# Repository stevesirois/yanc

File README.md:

# YANC
Y.A.N.C. - Yet Another Nixie Clock

This project is the software part of a larger project that include nixie tube clock with no physical controls but only "web" access.

The physical construction will be publish on Instructables (http://www.instructables.com/)

The project is two parts:

Physical part - Nixie Clock

- 4 nixie tubes (IN-14) display
- Raspberry PI Model A+ (256MB) for main controller
- Custom nixie driver circuit and audio ouput (PCB)
- MP3 Playback for alarm
- Sound activated display (extented life of tubes)

Software part - Clock control and remote app

- Controler daemon for clock hardware control (Python)
- REST Server to interact with external world (look mom, no button!)
- IOS App to "talk" to the clock (Swift)

Simply put, this clock will look great, will sync itself on the Net and get it's alarms from my Google Calendar! :-)

More details coming...

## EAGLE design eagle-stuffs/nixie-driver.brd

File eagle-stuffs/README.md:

# Eagle 7.2 files
The .sch and .brd files are Eagle CAD schematic and PCB design files.

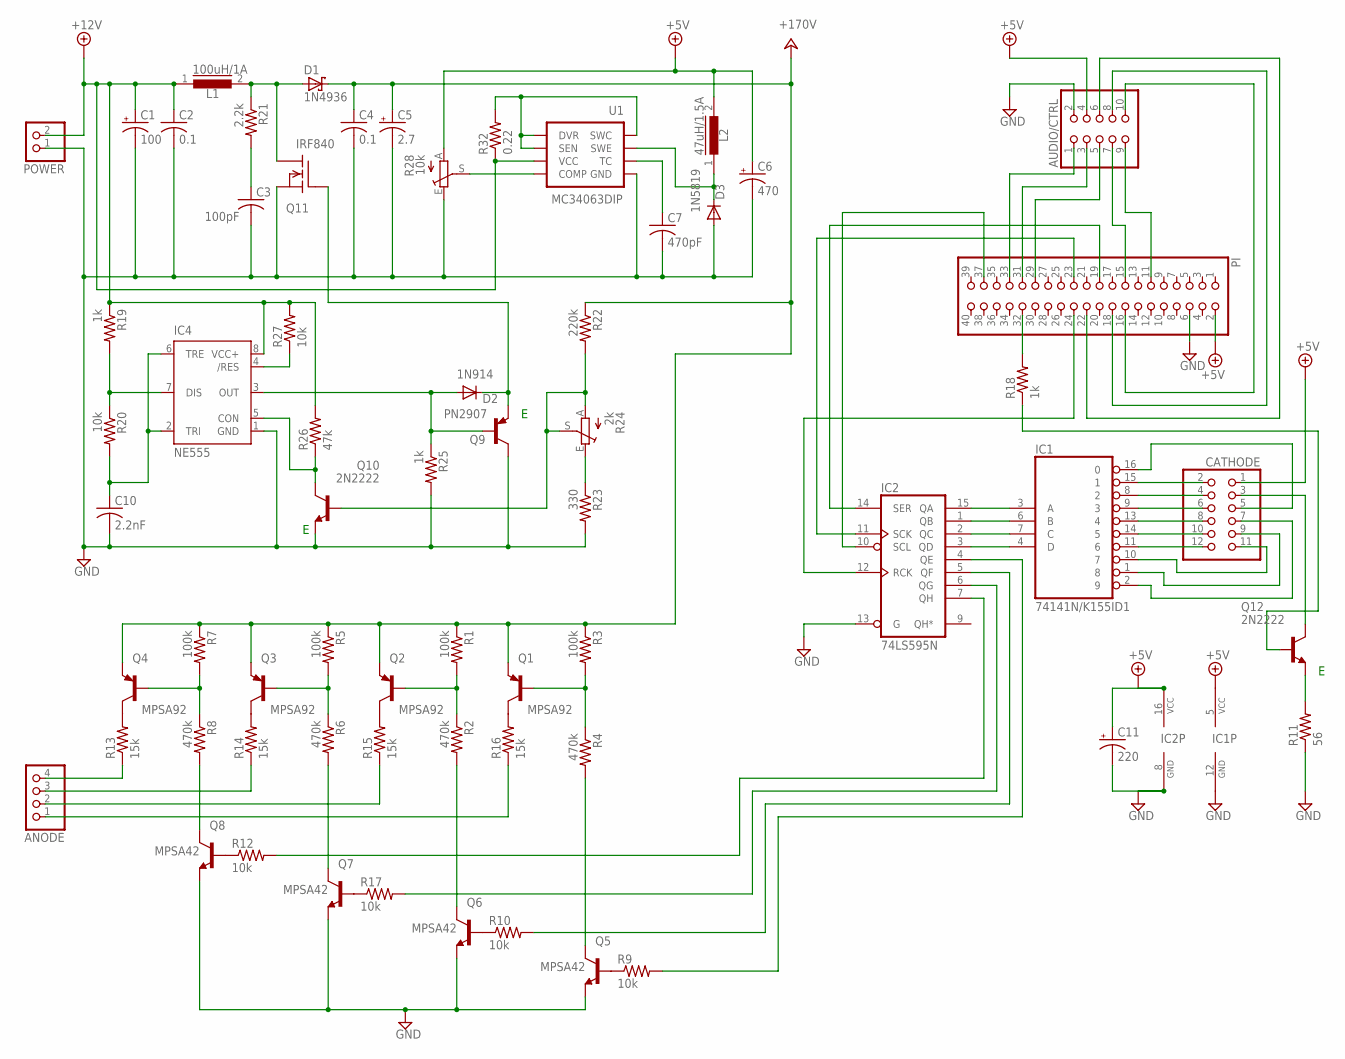
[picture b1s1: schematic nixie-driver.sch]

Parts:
ANODE: PINHD-1X4; 1X04
AUDIO/CTRL: PINHD-2X5; 2X05
C1: 100; E2,5-6E
C2: 0.1; C050-024X044
C3: 100pF; C050-024X044
C4: 0.1; C150-054X183
C5: 2.7; E2,5-7
C6: 470; E3,5-8
C7: 470pF; C050-024X044
C10: 2.2nF; C025-025X050
C11: 220; E3,5-8
CATHODE: PINHD-2X6; 2X06
D1: 1N4936; DO41-7.6
D2: 1N914; DO41-10
D3: 1N5819; DO41-10
IC1: 74141N/K155ID1; DIL16
IC2: 74LS595N; DIL16
IC4: NE555; DIL-08
L1: 100uH/1A; MMICC7
L2: 47uH/1.5A; MMICC7
PI: PINHD-2X20; 2X20
POWER: PINHD-1X2; 1X02
Q1, Q2, Q3, Q4: MPSA92; TO92-EBC
Q5, Q6, Q7, Q8: MPSA42; TO92-EBC
Q9: PN2907; TO92-CBE
Q10, Q12: 2N2222; TO92-EBC
Q11: IRF840; TO220
R1, R3, R5, R7: 100k; 0207/10
R2, R4, R6, R8: 470k; 0207/10
R9, R10, R12, R17, R20, R27: 10k; 0207/10
R11: 56; 0207/10
R13, R14, R15, R16: 15k; 0207/10
R18, R19, R25: 1k; 0207/10
R21: 2.2k; 0207/10
R22: 220k; 0207/10
R23: 330; 0207/10
R24: 2k; CA6V
R26: 47k; 0207/10
R28: 10k; CA6V
R32: 0.22; 0204V
U1: MC34063DIP; DIP-08

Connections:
+5V: AUDIO/CTRL.4, C6.+, C11.+, CATHODE.1, IC1.5 (VCC), IC2.16 (VCC), L2.2, PI.2, R28.A
+12V: C1.+, C2.1, IC4.8 (VCC+), L1.1, POWER.2, R19.1, R26.2, R27.2, R32.1, U1.6 (VCC)
+24V: C4.1, C5.+, D1.C, Q1.E, Q2.E, Q3.E, Q4.E, R1.1, R3.1, R5.1, R7.1, R22.1
GND: AUDIO/CTRL.2, C1.-, C2.2, C3.2, C4.2, C5.-, C6.-, C7.2, C10.2, C11.-, D3.A, IC1.12 (GND), IC2.8 (GND), IC2.13 (G), IC4.1 (GND), PI.6, POWER.1, Q5.E, Q6.E, Q7.E, Q8.E, Q9.C, Q10.E, Q11.3 (S), R11.1, R23.2, R25.2, R28.E, U1.4 (GND)
unnamed: D1.A, L1.2, Q11.2 (D), R21.1
unnamed: CATHODE.2, IC1.15 (1)
unnamed: CATHODE.4, IC1.8 (2)
unnamed: CATHODE.6, IC1.9 (3)
unnamed: CATHODE.8, IC1.13 (4)
unnamed: CATHODE.10, IC1.14 (5)
unnamed: CATHODE.12, IC1.11 (6)
unnamed: CATHODE.11, IC1.10 (7)
unnamed: CATHODE.9, IC1.1 (8)
unnamed: CATHODE.7, IC1.2 (9)
unnamed: CATHODE.5, IC1.16 (0)
unnamed: IC1.3 (A), IC2.15 (QA)
unnamed: IC1.6 (B), IC2.1 (QB)
unnamed: IC1.7 (C), IC2.2 (QC)
unnamed: IC1.4 (D), IC2.3 (QD)
unnamed: PI.32, R18.2
unnamed: Q4.B, R7.2, R8.1
unnamed: Q3.B, R5.2, R6.1
unnamed: Q2.B, R1.2, R2.1
unnamed: Q1.B, R3.2, R4.1
unnamed: Q4.C, R13.2
unnamed: Q3.C, R14.2
unnamed: Q2.C, R15.2
unnamed: Q1.C, R16.2
unnamed: ANODE.4, R13.1
unnamed: ANODE.3, R14.1
unnamed: ANODE.2, R15.1
unnamed: ANODE.1, R16.1
unnamed: Q8.C, R8.2
unnamed: Q8.B, R12.1
unnamed: Q7.B, R17.1
unnamed: Q6.B, R10.1
unnamed: Q5.B, R9.1
unnamed: Q7.C, R6.2
unnamed: Q6.C, R2.2
unnamed: Q5.C, R4.2
unnamed: IC2.7 (QH), R12.2
unnamed: IC2.6 (QG), R17.2
unnamed: IC2.5 (QF), R10.2
unnamed: IC2.4 (QE), R9.2
unnamed: IC2.12 (RCK), PI.24
unnamed: IC2.11 (SCK), PI.23
unnamed: IC2.14 (SER), PI.19
unnamed: Q12.E, R11.2
unnamed: CATHODE.3, Q12.C
unnamed: Q12.B, R18.1
unnamed: AUDIO/CTRL.1, PI.33
unnamed: AUDIO/CTRL.3, PI.31
unnamed: AUDIO/CTRL.5, PI.29
unnamed: AUDIO/CTRL.7, PI.15
unnamed: AUDIO/CTRL.9, PI.11
unnamed: IC4.7 (DIS), R19.2, R20.1
unnamed: AUDIO/CTRL.10, PI.16
unnamed: AUDIO/CTRL.8, PI.18
unnamed: AUDIO/CTRL.6, PI.22
unnamed: C3.1, R21.2
unnamed: R32.2, U1.1 (SWC), U1.7 (SEN), U1.8 (DVR)
unnamed: IC4.4 (/RES), R27.1
unnamed: D2.A, IC4.3 (OUT), Q9.B, R25.1
unnamed: IC4.5 (CON), Q10.C, R26.1
unnamed: R28.S, U1.5 (COMP)
unnamed: D2.C, Q9.E, Q11.1 (G)
unnamed: IC2.10 (SCL), PI.37
unnamed: Q10.B, R22.2, R24.A, R24.S
unnamed: R23.1, R24.E
unnamed: C10.1, IC4.2 (TRI), IC4.6 (TRE), R20.2
unnamed: C7.1, U1.3 (TC)
unnamed: D3.C, L2.1, U1.2 (SWE)

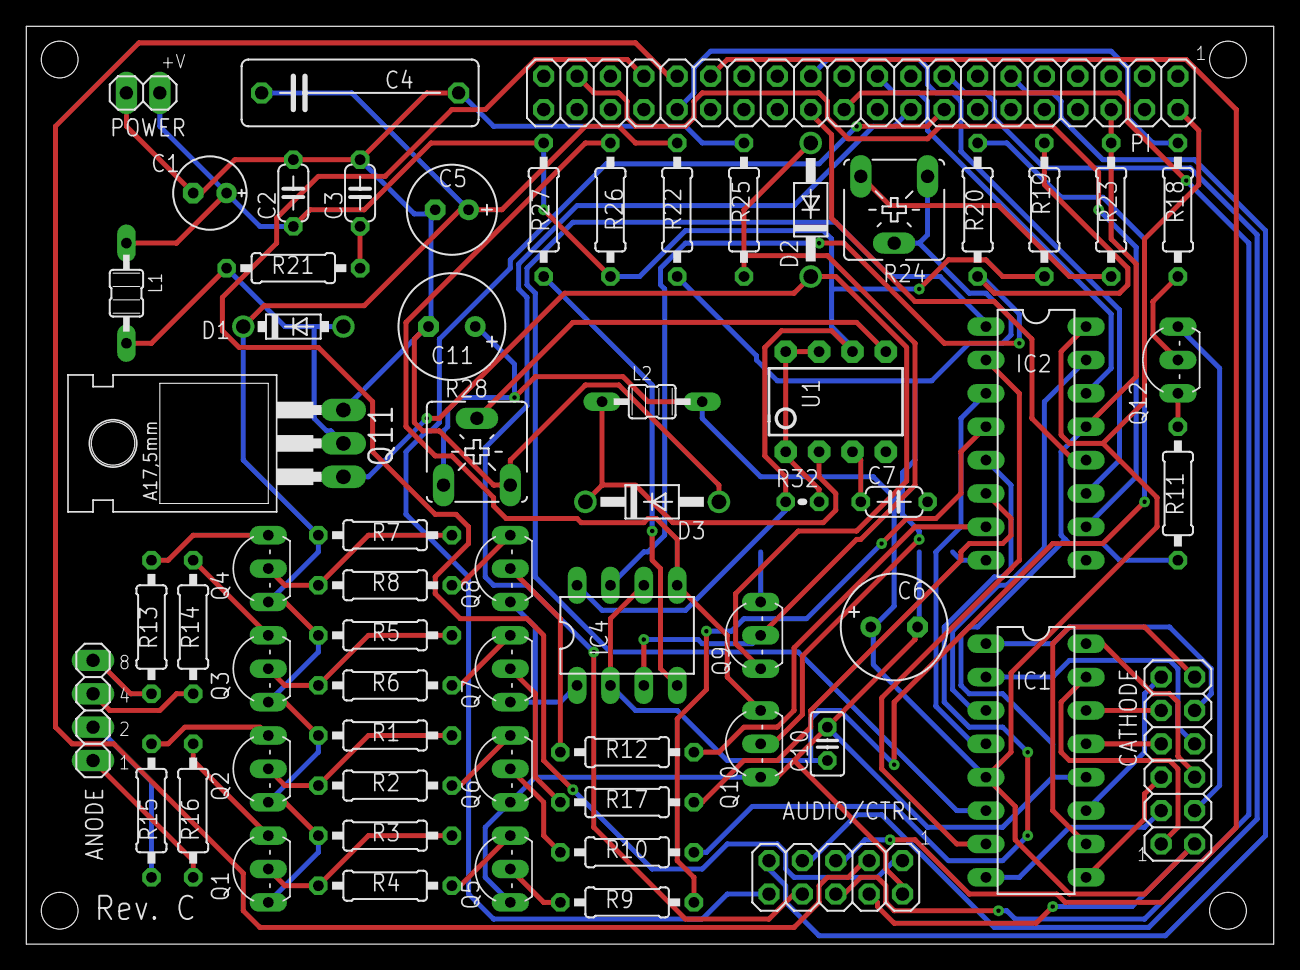
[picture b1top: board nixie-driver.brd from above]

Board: 2 copper layers, 94.9 x 69.8 mm, 64 parts (0 on the bottom side), 72 nets.

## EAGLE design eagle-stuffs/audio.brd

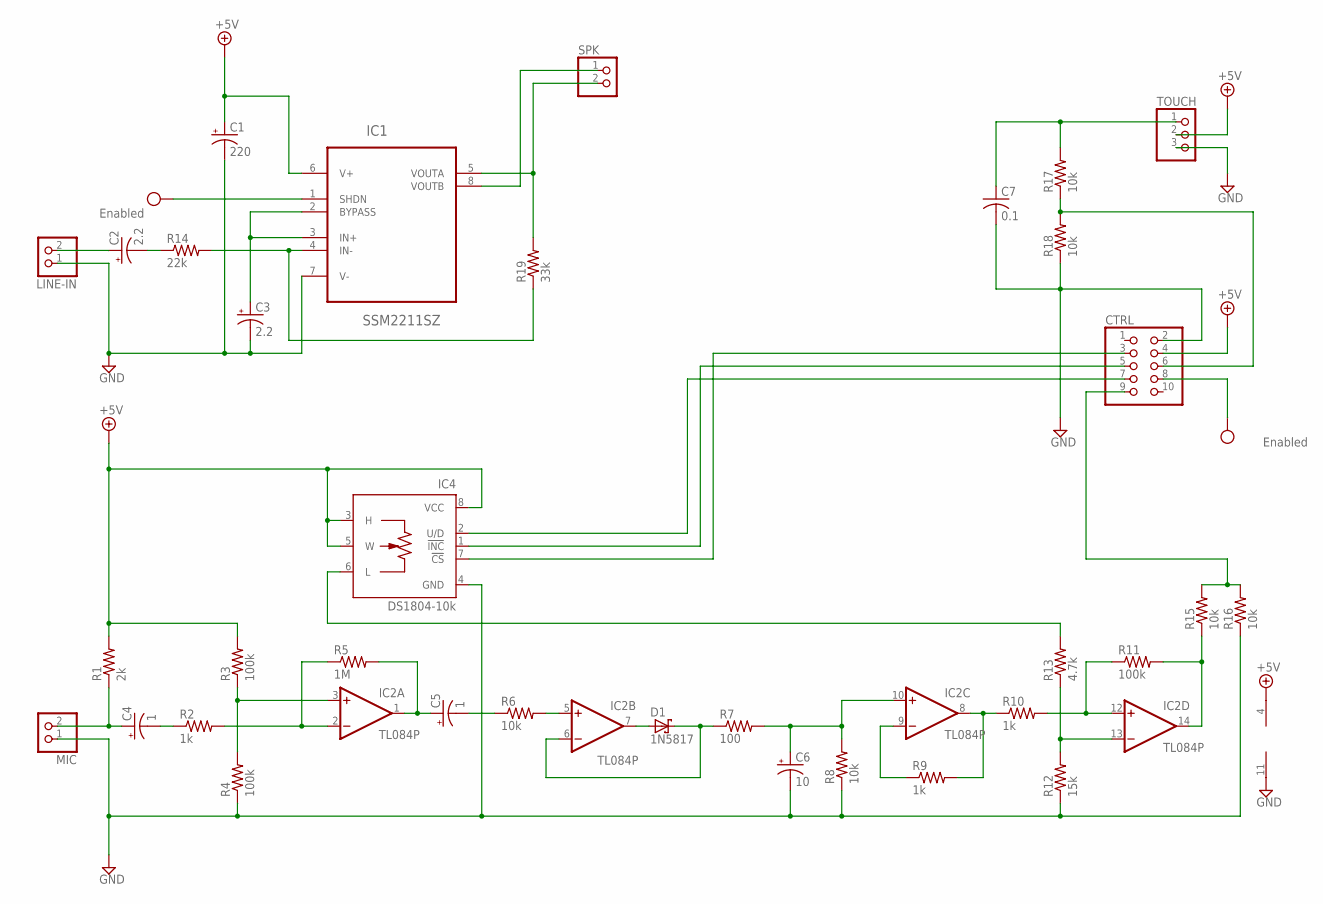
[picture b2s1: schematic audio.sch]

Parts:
C1: 220; E3,5-10
C2, C3: 2.2; E3,5-8
C4, C5: 1; E2-4
C6: 10; E2-4
C7: 0.1; C025-024X044
CTRL: PINHD-2X5; 2X05
D1: 1N5817; DO41-7
IC1: SSM2211SZ; SOIC127P600X175-8N
IC2: TL084P; DIL14
IC4: DS1804-10k; DIL08
LINE-IN: PINHD-1X2; 1X02
MIC: PINHD-1X2; 1X02
R1: 2k; 0204V
R2, R9, R10: 1k; 0204V
R3, R4, R11: 100k; 0204V
R5: 1M; 0204V
R6, R8, R15, R16, R17, R18: 10k; 0204V
R7: 100; 0204V
R12: 15k; 0204V
R13: 4.7k; 0204V
R14: 22k; 0204V
R19: 33k; 0204V
SPK: PINHD-1X2; 1X02
TOUCH: PINHD-1X3; 1X03

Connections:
+5V: C1.+, CTRL.4, IC1.6 (V+), IC2.4 (V+), IC4.3 (H), IC4.5 (W), IC4.8 (VCC), R1.2, R3.2, TOUCH.2
GND: C1.-, C3.-, C6.-, C7.2, CTRL.2, IC1.7 (V-), IC2.11 (V-), IC4.4 (GND), LINE-IN.1, MIC.1, R4.1, R8.1, R12.1, R16.1, R18.1, TOUCH.3
unnamed: IC1.5 (VOUTA), R19.2, SPK.2
unnamed: C2.+, LINE-IN.2
unnamed: C2.-, R14.1
unnamed: IC1.4 (IN-), R14.2, R19.1
unnamed: C3.+, IC1.2 (BYPASS), IC1.3 (IN+)
unnamed: IC1.8 (VOUTB), SPK.1
unnamed: IC4.6 (L), R13.2
unnamed: C4.-, R2.1
unnamed: C4.+, MIC.2, R1.1
unnamed: IC2.2 (-IN), R2.2, R5.1
unnamed: C5.+, IC2.1 (OUT), R5.2
unnamed: C5.-, R6.1
unnamed: IC2.14 (OUT), R11.2, R15.1
unnamed: IC2.3 (+IN), R3.1, R4.2
unnamed: CTRL.9, R15.2, R16.2
unnamed: D1.A, IC2.7 (OUT)
unnamed: IC2.5 (+IN), R6.2
unnamed: CTRL.3, IC4.7 (!CS)
unnamed: CTRL.5, IC4.1 (!INC)
unnamed: CTRL.7, IC4.2 (U/D)
unnamed: D1.C, IC2.6 (-IN), R7.1
unnamed: C6.+, IC2.10 (+IN), R7.2, R8.2
unnamed: IC2.9 (-IN), R9.1
unnamed: IC2.8 (OUT), R9.2, R10.1
unnamed: IC2.12 (+IN), R10.2, R11.1
unnamed: C7.1, R17.2, TOUCH.1
unnamed: IC2.13 (-IN), R12.2, R13.1
unnamed: CTRL.6, R17.1, R18.2
VCC: CTRL.8, IC1.1 (SHDN)

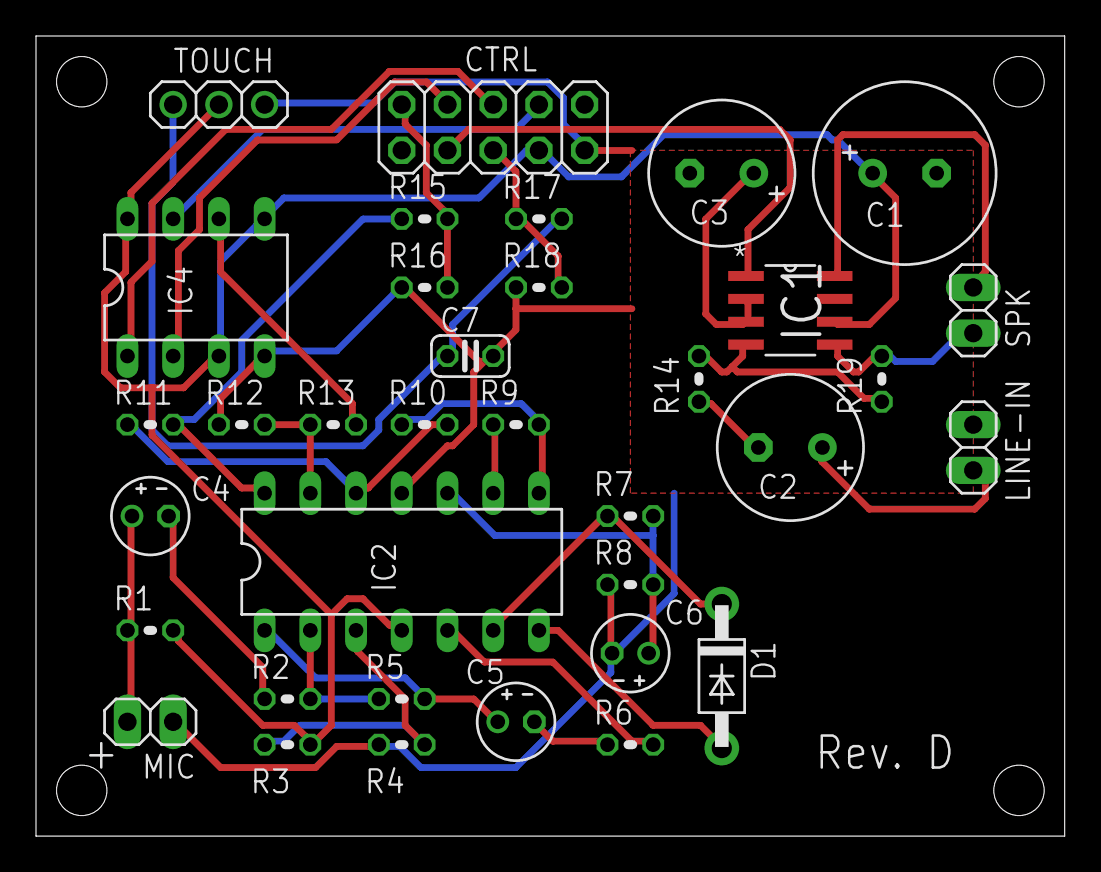
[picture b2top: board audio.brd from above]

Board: 2 copper layers, 57.1 x 44.5 mm, 35 parts (0 on the bottom side), 31 nets.

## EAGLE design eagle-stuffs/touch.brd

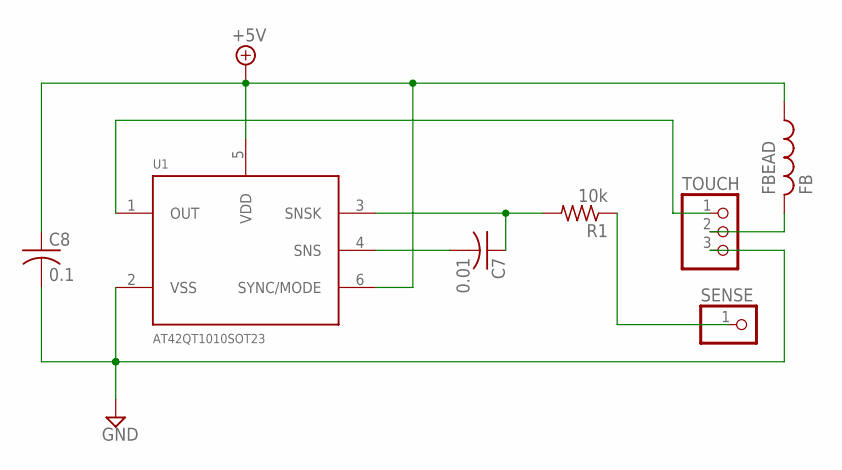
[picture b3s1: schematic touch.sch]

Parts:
C7: 0.01; C025-025X050
C8: 0.1; C025-025X050
FBEAD: FB
R1: 10k; 0207/10
SENSE: PINHD-1X1; 1X01
TOUCH: PINHD-1X3; 1X03
U1: AT42QT1010SOT23; SOT23-6

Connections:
+5V: C8.1, FBEAD.P$1 (1), U1.5 (VDD), U1.6 (SYNC/MODE)
GND: C8.2, TOUCH.3, U1.2 (VSS)
unnamed: TOUCH.1, U1.1 (OUT)
unnamed: R1.1, SENSE.1
unnamed: FBEAD.P$2 (2), TOUCH.2
unnamed: C7.1, R1.2, U1.3 (SNSK)
unnamed: C7.2, U1.4 (SNS)

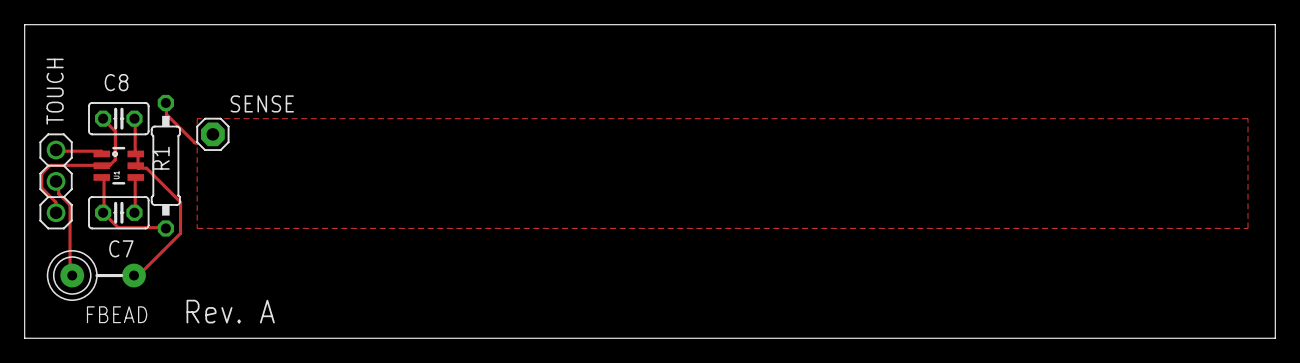
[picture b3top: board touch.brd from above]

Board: 2 copper layers, 101.3 x 25.4 mm, 7 parts (0 on the bottom side), 7 nets.

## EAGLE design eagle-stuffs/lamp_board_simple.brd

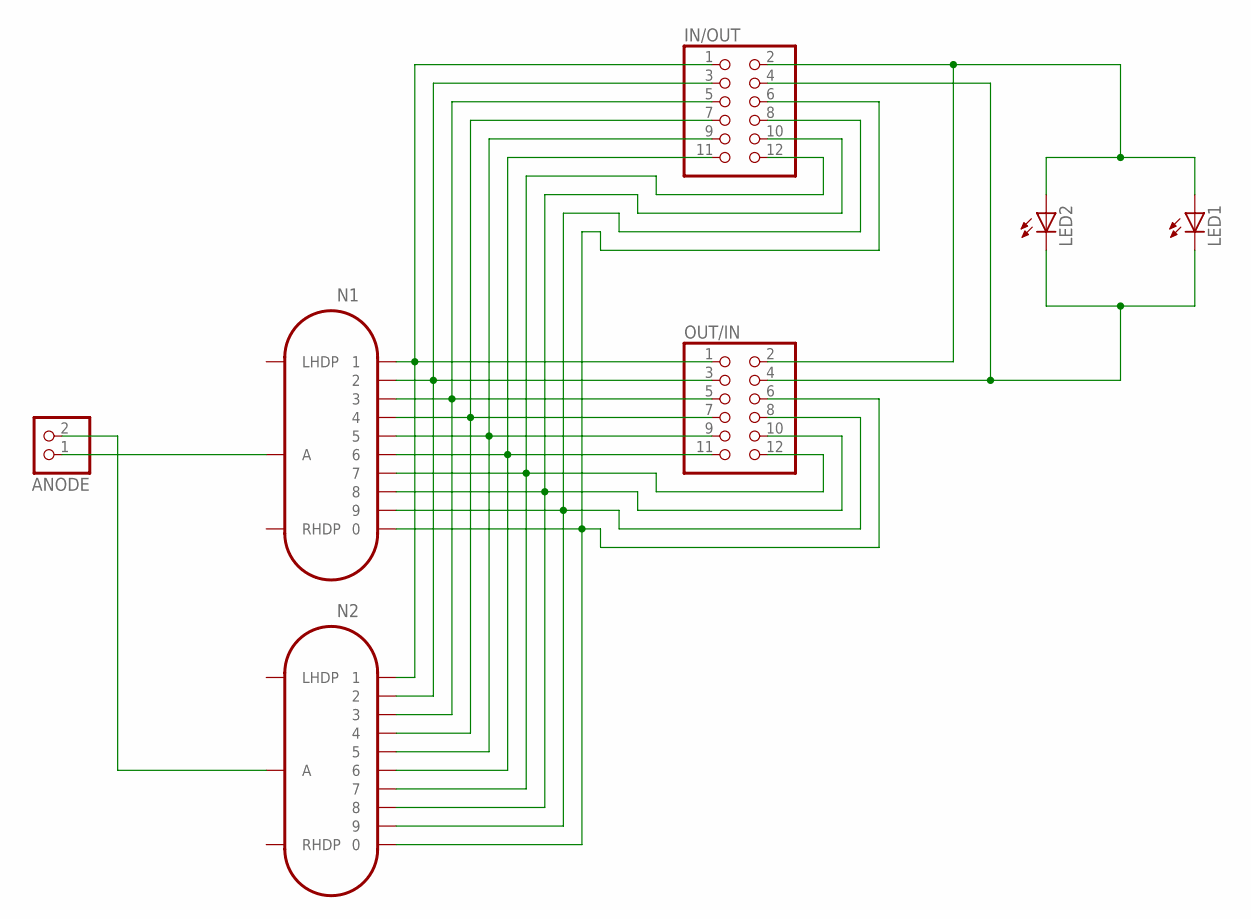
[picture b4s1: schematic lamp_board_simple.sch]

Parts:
ANODE: PINHD-1X2/90; 1X02/90
IN/OUT: PINHD-2X6/90; 2X06/90
LED1, LED2: LED5MM
N1, N2: IN-14
OUT/IN: PINHD-2X6/90; 2X06/90

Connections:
unnamed: ANODE.1, N1.A
unnamed: ANODE.2, N2.A
unnamed: IN/OUT.4, LED1.K (C), LED2.K (C), OUT/IN.4
unnamed: IN/OUT.2, LED1.A, LED2.A, OUT/IN.2
unnamed: IN/OUT.1, N1.1, N2.1, OUT/IN.1
unnamed: IN/OUT.3, N1.2, N2.2, OUT/IN.3
unnamed: IN/OUT.5, N1.3, N2.3, OUT/IN.5
unnamed: IN/OUT.7, N1.4, N2.4, OUT/IN.7
unnamed: IN/OUT.9, N1.5, N2.5, OUT/IN.9
unnamed: IN/OUT.11, N1.6, N2.6, OUT/IN.11
unnamed: IN/OUT.12, N1.7, N2.7, OUT/IN.12
unnamed: IN/OUT.10, N1.8, N2.8, OUT/IN.10
unnamed: IN/OUT.8, N1.9, N2.9, OUT/IN.8
unnamed: IN/OUT.6, N1.0, N2.0, OUT/IN.6

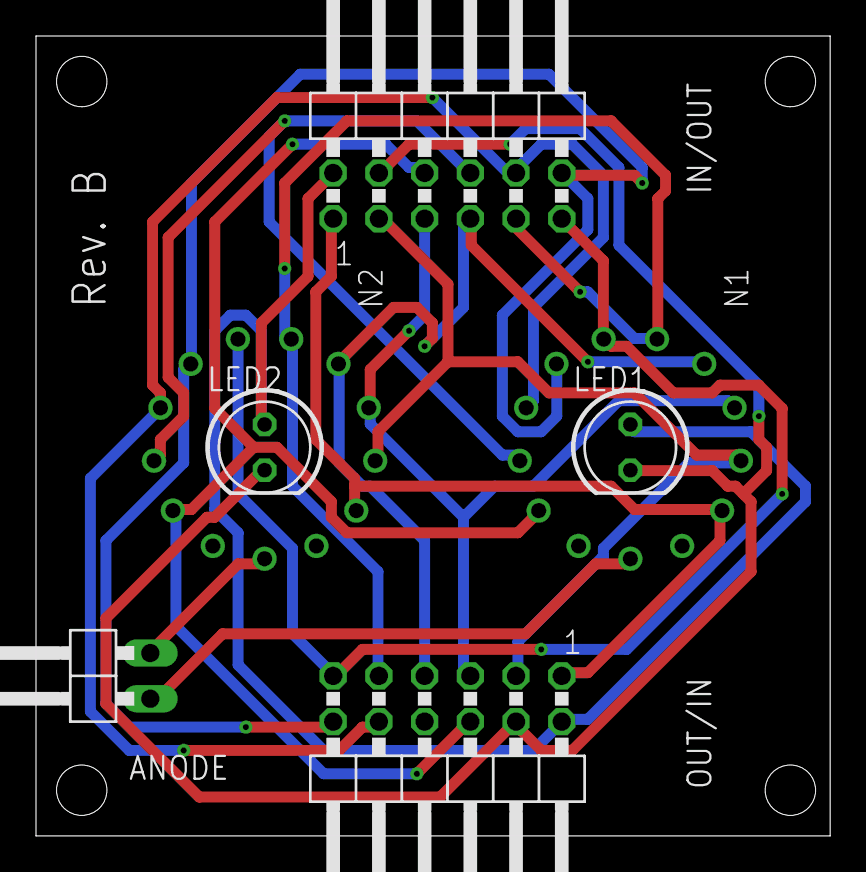
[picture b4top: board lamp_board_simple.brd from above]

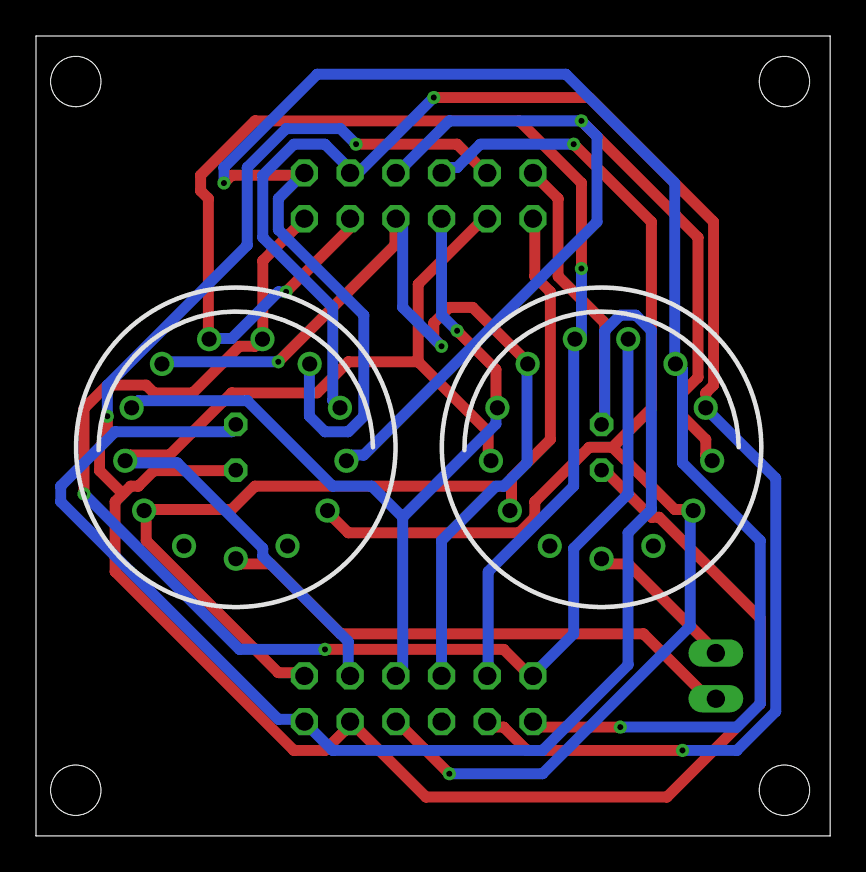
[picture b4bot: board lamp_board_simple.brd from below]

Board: 2 copper layers, 44.1 x 44.4 mm, 7 parts (2 on the bottom side), 14 nets.

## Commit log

2015-05-28 Create LICENSE
2015-05-29 Initiale creation
2015-05-29 First add
2015-05-29 Added overview
2015-05-30 Start to frame the thing
2015-05-30 Small characters stuff
2015-05-30 Add licence notice
2015-05-30 Add beta audio
2015-05-30 Remove useless stuff
2015-05-31 some more
2015-05-31 More ignore
2015-05-31 Working on audio board
2015-06-01 Still working on audio…
2015-06-01 Found SSM2211 lib… still going
2015-06-01 Cosmetic ajustement
2015-06-01 This should work…
2015-06-02 Waiting for proto board test design
2015-06-02 Final beta
2015-06-02 Capacitive board
2015-06-09 Updated something
2015-06-11 Minor stuffs
2015-06-15 Exclude private stuff
2015-06-17 Layout adjustement
    Adjusted some physical component size & layout
2015-06-18 Add revision info
2015-06-18 Mirror cathod connector
    Corrected major layout error!!! Needed to mirror cathod connector since
    it mounted on bottom layer on lamp board and not on this board. Blowed
    up my Pi this morning for the maiden test of the board :-(
2015-06-18 Updated after cathod mirrored
2015-06-18 Ajustements to silk
2015-06-18 Minor ajustements
2015-06-18 Changed some drilling size
2015-06-19 Corrected mirror pinout on nixie
2015-06-19 Updated to rev. b
2015-06-19 Added some info
2015-06-21 Final version
2015-06-21 C1 value changed
2015-06-21 Added some more info
2015-07-06 adjusted value of digital pot
2015-07-06 Getting things shape up!
2015-07-06 Corrected pin assignment and some cleanup
2015-07-07 First stable version - just showing time :-S
2015-07-07 Dummy version of this private info file
2015-07-07 Move back led-brightness() at is place!
    Doing too much cleanup…
2015-07-09 Added voltage divider on output
    I forgot I was dealing with 3.3v input chip! :-(
2015-07-09 Remove bottom side - now single-sided pcb
2015-07-15 Discarded the TPS562209
    Too sensitive to touch (touching the chip, blow-it up!
2015-07-15 Removed second digital pot
2015-07-15 Inverted input on follower section for mic
2015-07-17 Ajusted layout + add backplane shield
2015-07-17 Work in progress
2015-07-19 Change R13 value
    Going at 10k on the digit pot will have the reverse effect on gain and
    shutdown the mic.
2015-07-19 Put the REST server on separate file
    The standalone Flask server was not very stable inside a child process.
2015-07-19 Divorce from REST. Check yanc-REST
2015-07-22 Put back if __name__ for easier local testing
2015-07-22 First working version in daemon mode
2015-07-22 Clean daemon! Everything got's to be better from here :-)
2015-07-23 Renaming some variables
2015-07-24 Added sensors functions
2015-07-27 Getting there!
2015-07-28 Added some msg handling in show_nixie
2015-07-28 Change fixed resistors for voltage output ajust. to pot.
    The PI seems to be quite touchy about the voltage drop under load. Got
    to push it to 5.1v to make the red led stop to blink!

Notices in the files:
eagle-stuffs/audio.sch:
Licensed under CERN OHL v.1.2 or later
parts and their libraries:
SparkFun-PowerIC: Licensing: Creative Commons ShareAlike 4.0 International - https://creativecommons.org/licenses/by-sa/4.0
SparkFun-DigitalIC: Licensing: CC v3.0 Share-Alike You are welcome to use this library for commercial purposes.
